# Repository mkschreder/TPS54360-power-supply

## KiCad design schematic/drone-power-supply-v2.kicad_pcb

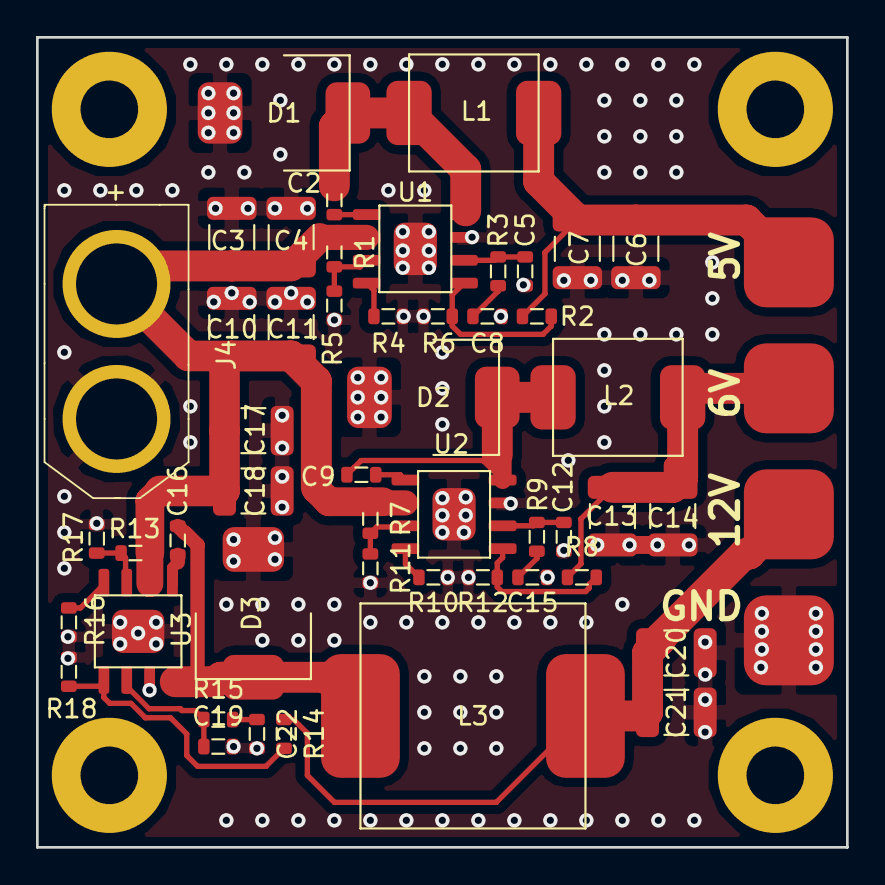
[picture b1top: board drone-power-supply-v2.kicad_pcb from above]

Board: 2 copper layers, 45.0 x 45.0 mm, 57 parts (0 on the bottom side), 26 nets.

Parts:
C2, C9, C16: CAP_100nF_10V; CAPC1608X09N
C3, C4, C10, C11, C17, C18: CAP_10uF_63V; CAPC3225X25N
C5, C12, C19: CAP_39pF_16V; CAPC1608X09N
C6, C7, C13, C14, C20, C21: CAP_47uF_16V; CAPC3225X25N
C8, C15, C22: CAP_8200pF_10V; CAPC1608X09N
D1, D2, D3: D_B520C; DIOM7162X25N
J1, J2, J3, J5: POWER_PAD; PCB_WirePad_5mm
J4: CONN_XT60; XT60
L1, L2: L_8.2uH_4.5A; INDM7265X40N
L3: L_15uH_5A; INDM125125X60N
MT1, MT2, MT3, MT4: MOUNT_HOLE; MountingHole_3.2mm_M3_Pad
R1, R7, R13: RES_523K_1%; RESC1608X04N
R2: RES_53.6K_1%; RESC1608X04N
R3: RES_13K_1%; RESC1608X04N
R4: RES_162K_1%; RESC1608X04N
R5, R11, R17: RES_84.5K_1%; RESC1608X04N
R6, R12, R18: RES_10.2K_1%; RESC1608X04N
R8: RES_66.5K_1%; RESC1608X04N
R9: RES_18K_1%; RESC1608X04N
R10, R16: RES_100K_1%; RESC1608X04N
R14: RES_143K_1%; RESC1608X04N
R15: RES_25.5K_1%; RESC1608X04N
U1, U2, U3: TPS54360DDA; SOIC127P600X175_HS-9N

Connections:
/PWR_5V_SW: C2.2, D1.1, L1.1, U1.8
/PWR_6V_SW: C9.2, D2.1, L2.1, U2.8
/PWR_12V_SW: C16.2, D3.1, L3.1, U3.8
/PWR_OUT_5V: C6.1, C7.1, J1.1, L1.2, R2.1
/PWR_OUT_6V: C13.1, C14.1, J2.1, L2.2, R8.1
/PWR_OUT_12V: C20.1, C21.1, J3.1, L3.2, R14.1
GND: C3.2, C4.2, C5.2, C6.2, C7.2, C8.2, C10.2, C11.2, C12.2, C13.2, C14.2, C15.2, C17.2, C18.2, C19.2, C20.2, C21.2, C22.2, D1.2, D2.2, D3.2, J4.1, J5.1, R4.2, R5.2, R6.2, R10.2, R11.2, R12.2, R16.2, R17.2, R18.2, U1.7, U1.9, U2.7, U2.9, U3.7, U3.9
unnamed: C2.1, U1.1
unnamed: C5.1, R3.1, U1.6
unnamed: C8.1, R3.2
unnamed: C9.1, U2.1
unnamed: C12.1, R9.1, U2.6
unnamed: C15.1, R9.2
unnamed: C16.1, U3.1
unnamed: C19.1, R15.1, U3.6
unnamed: C22.1, R15.2
unnamed: R1.2, R5.1, U1.3
unnamed: R2.2, R6.1, U1.5
unnamed: R4.1, U1.4
unnamed: R10.1, U2.4
unnamed: R7.2, R11.1, U2.3
unnamed: R8.2, R12.1, U2.5
unnamed: R13.2, R17.1, U3.3
unnamed: R14.2, R18.1, U3.5
unnamed: R16.1, U3.4
VBAT: C3.1, C4.1, C10.1, C11.1, C17.1, C18.1, J4.2, R1.1, R7.1, R13.1, U1.2, U2.2, U3.2

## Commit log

2018-03-19 Add bom
2018-03-19 add initial schematic for 5v regulator
2018-03-19 add initial board placement and 6 + 12v regulators
2018-04-04 push latest changes
